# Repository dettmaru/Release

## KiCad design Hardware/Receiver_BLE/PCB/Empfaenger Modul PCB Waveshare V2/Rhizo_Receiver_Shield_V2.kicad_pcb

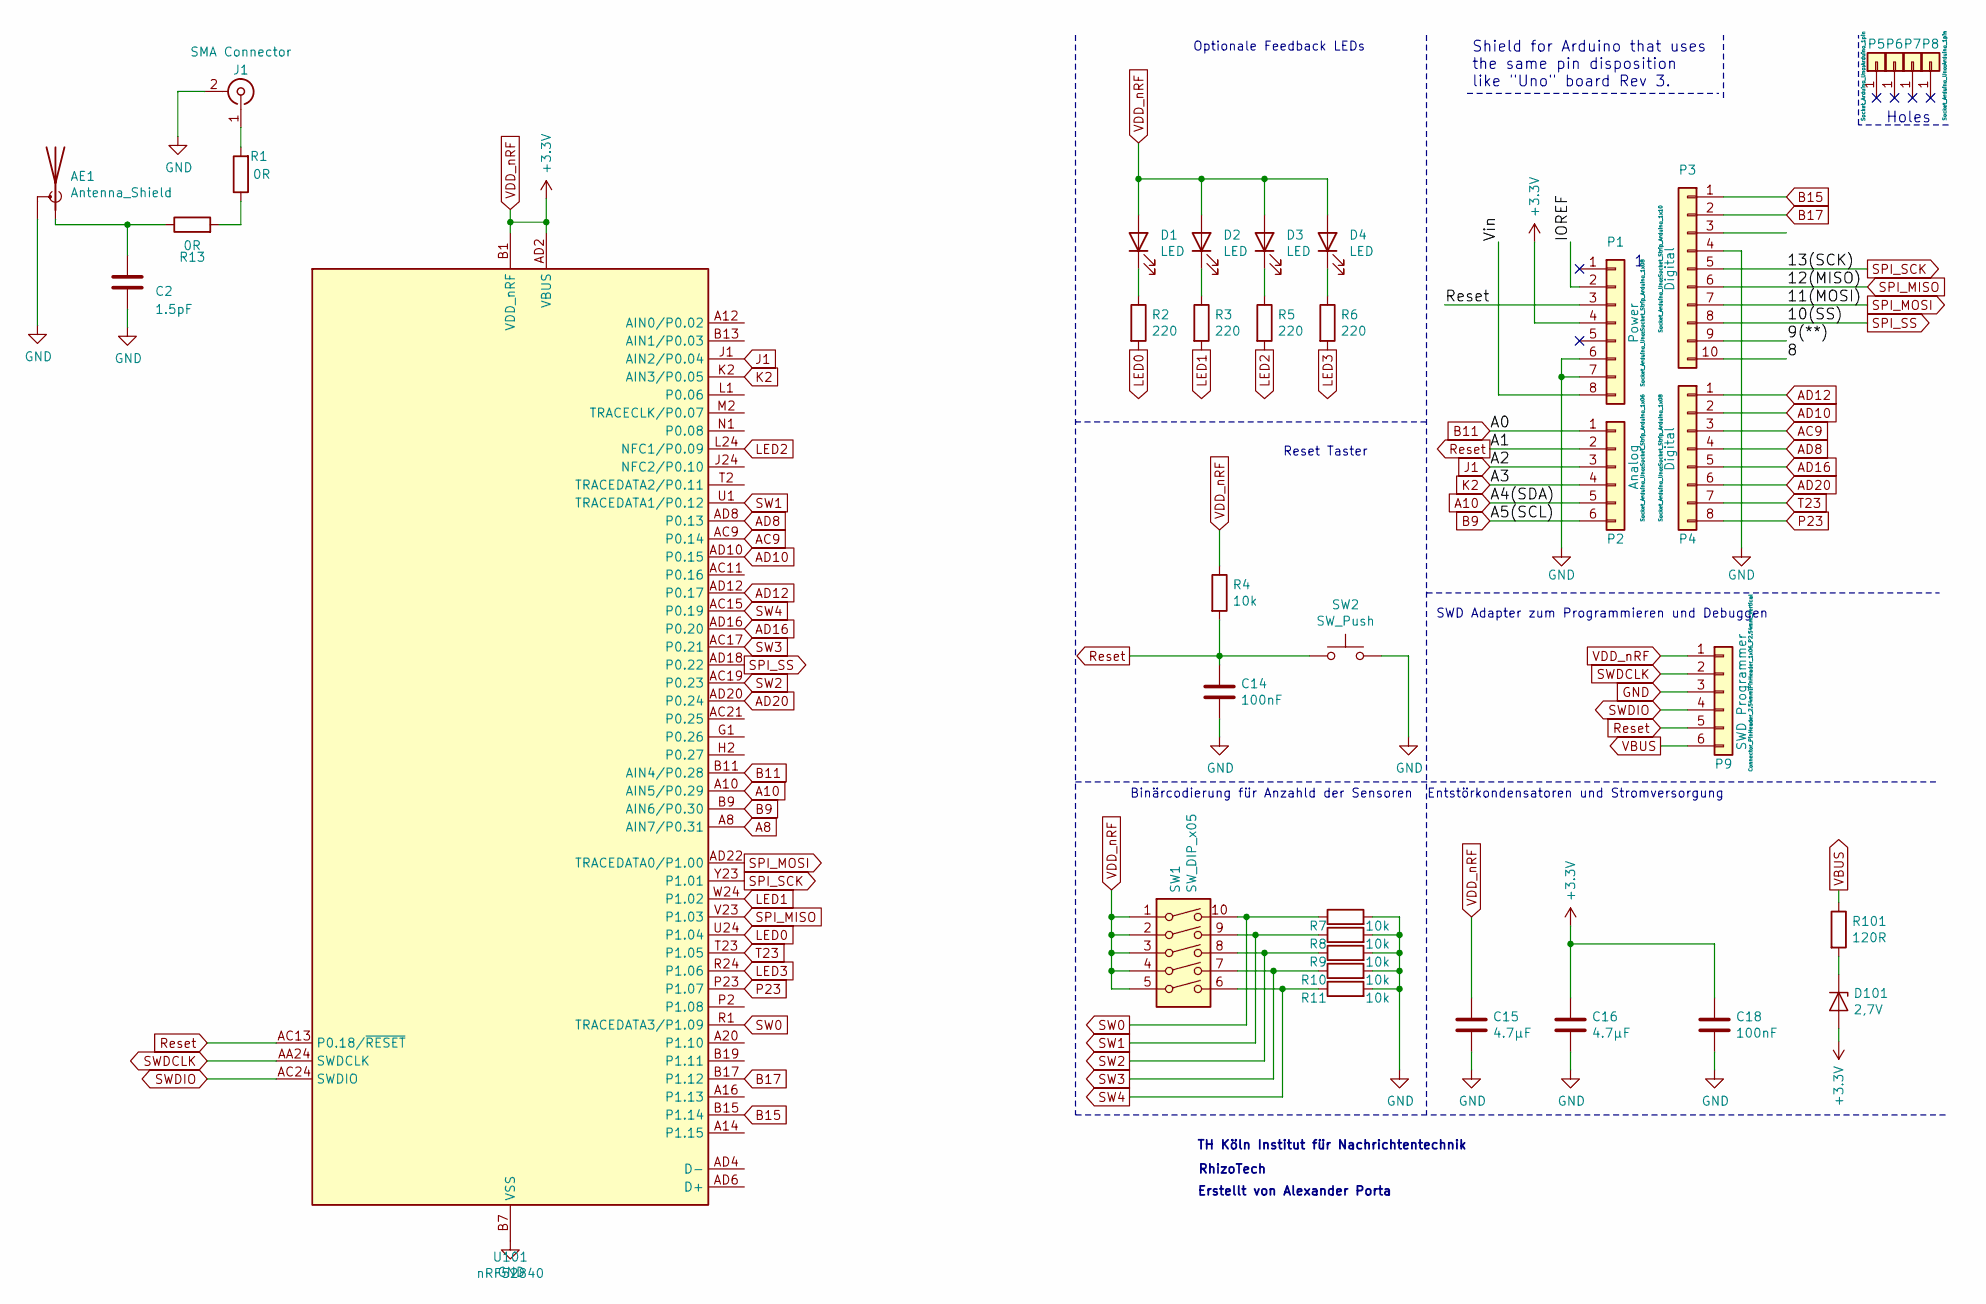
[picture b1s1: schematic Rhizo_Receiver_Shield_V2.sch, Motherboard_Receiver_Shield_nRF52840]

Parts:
AE1: Antenna_Shield; Texas_SWRA117D_2.4GHz_Left
C2: 1.5pF; C_0603_1608Metric_Pad1.08x0.95mm_HandSolder
C14, C18: 100nF; C_0603_1608Metric_Pad1.08x0.95mm_HandSolder
C15, C16: 4.7µF; C_0603_1608Metric_Pad1.08x0.95mm_HandSolder
D1, D2, D3, D4: LED; LED_0603_1608Metric
D101: 2,7V; D_0603_1608Metric
J1: SMA Connector; U.FL_Hirose_U.FL-R-SMT-1_Vertical
P1: Power; Socket_Strip_Arduino_1x08
P2: Analog; Socket_Strip_Arduino_1x06
P3: Digital; Socket_Strip_Arduino_1x10
P4: Digital; Socket_Strip_Arduino_1x08
P5, P6, P7, P8: CONN_01X01; Arduino_1pin
P9: SWD Programmer; PinHeader_1x06_P2.54mm_Vertical
R1, R13: 0R; R_0603_1608Metric
R2, R3, R5, R6: 220; R_0603_1608Metric
R4, R7, R8, R9, R10, R11: 10k; R_0603_1608Metric
R101: 120R; R_0603_1608Metric
SW1: SW_DIP_x05; SW_DIP_SPSTx05_Slide_6.7x14.26mm_W6.73mm_P2.54mm_LowProfile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
SW2: SW_Push; SW_SPST_EVQQ2
U101: nRF52840; Waveshare_nRF528840

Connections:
/8: P3.10
/9(**): P3.9
/IOREF: P1.2
/Vin: P1.8
A8: U101.A8 (AIN7/P0.31)
A10: P2.5, U101.A10 (AIN5/P0.29)
AC9: P4.3, U101.AC9 (P0.14)
AD8: P4.4, U101.AD8 (P0.13)
AD10: P4.2, U101.AD10 (P0.15)
AD12: P4.1, U101.AD12 (P0.17)
AD16: P4.5, U101.AD16 (P0.20)
AD20: P4.6, U101.AD20 (P0.24)
B9: P2.6, U101.B9 (AIN6/P0.30)
B11: P2.1, U101.B11 (AIN4/P0.28)
B15: P3.1, U101.B15 (P1.14)
B17: P3.2, U101.B17 (P1.12)
GND: AE1.2 (Shield), C2.2, C14.2, C15.2, C16.2, C18.2, J1.2 (Ext), P1.6, P1.7, P3.4, P9.3, R7.2, R8.2, R9.2, R10.2, R11.2, SW2.2, U101.B7 (VSS)
J1: P2.3, U101.J1 (AIN2/P0.04)
K2: P2.4, U101.K2 (AIN3/P0.05)
LED0: R2.2, U101.U24 (P1.04)
LED1: R3.2, U101.W24 (P1.02)
LED2: R5.2, U101.L24 (NFC1/P0.09)
LED3: R6.2, U101.R24 (P1.06)
unnamed: AE1.1 (A), C2.1, R13.1
unnamed: D1.1 (K), R2.1
unnamed: D2.1 (K), R3.1
unnamed: D3.1 (K), R5.1
unnamed: D4.1 (K), R6.1
unnamed: D101.1 (K), R101.2
unnamed: J1.1 (In), R1.2
unnamed: R1.1, R13.2
P23: P4.8, U101.P23 (P1.07)
Reset: C14.1, P1.3, P2.2, P9.5, R4.2, SW2.1, U101.AC13 (P0.18/~RESET)
SPI_MISO: P3.6, U101.V23 (P1.03)
SPI_MOSI: P3.7, U101.AD22 (TRACEDATA0/P1.00)
SPI_SCK: P3.5, U101.Y23 (P1.01)
SPI_SS: P3.8, U101.AD18 (P0.22)
SW0: R7.1, SW1.10, U101.R1 (TRACEDATA3/P1.09)
SW1: R8.1, SW1.9, U101.U1 (TRACEDATA1/P0.12)
SW2: R9.1, SW1.8, U101.AC19 (P0.23)
SW3: R10.1, SW1.7, U101.AC17 (P0.21)
SW4: R11.1, SW1.6, U101.AC15 (P0.19)
SWDCLK: P9.2, U101.AA24 (SWDCLK)
SWDIO: P9.4, U101.AC24 (SWDIO)
T23: P4.7, U101.T23 (P1.05)
VBUS: P9.6, R101.1
VDD_nRF: C15.1, C16.1, C18.1, D1.2 (A), D2.2 (A), D3.2 (A), D4.2 (A), D101.2 (A), P1.4, P9.1, R4.1, SW1.1, SW1.2, SW1.3, SW1.4, SW1.5, U101.AD2 (VBUS), U101.B1 (VDD_nRF)

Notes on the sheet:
Binärcodierung für Anzahld der Sensoren
Optionale Feedback LEDs
TH Köln Institut für Nachrichtentechnik
Erstellt von Alexander Porta
RhizoTech
Reset Taster
Entstörkondensatoren und Stromversorgung
SWD Adapter zum Programmieren und Debuggen
Shield for Arduino that uses the same pin disposition like "Uno" board Rev 3.
Holes

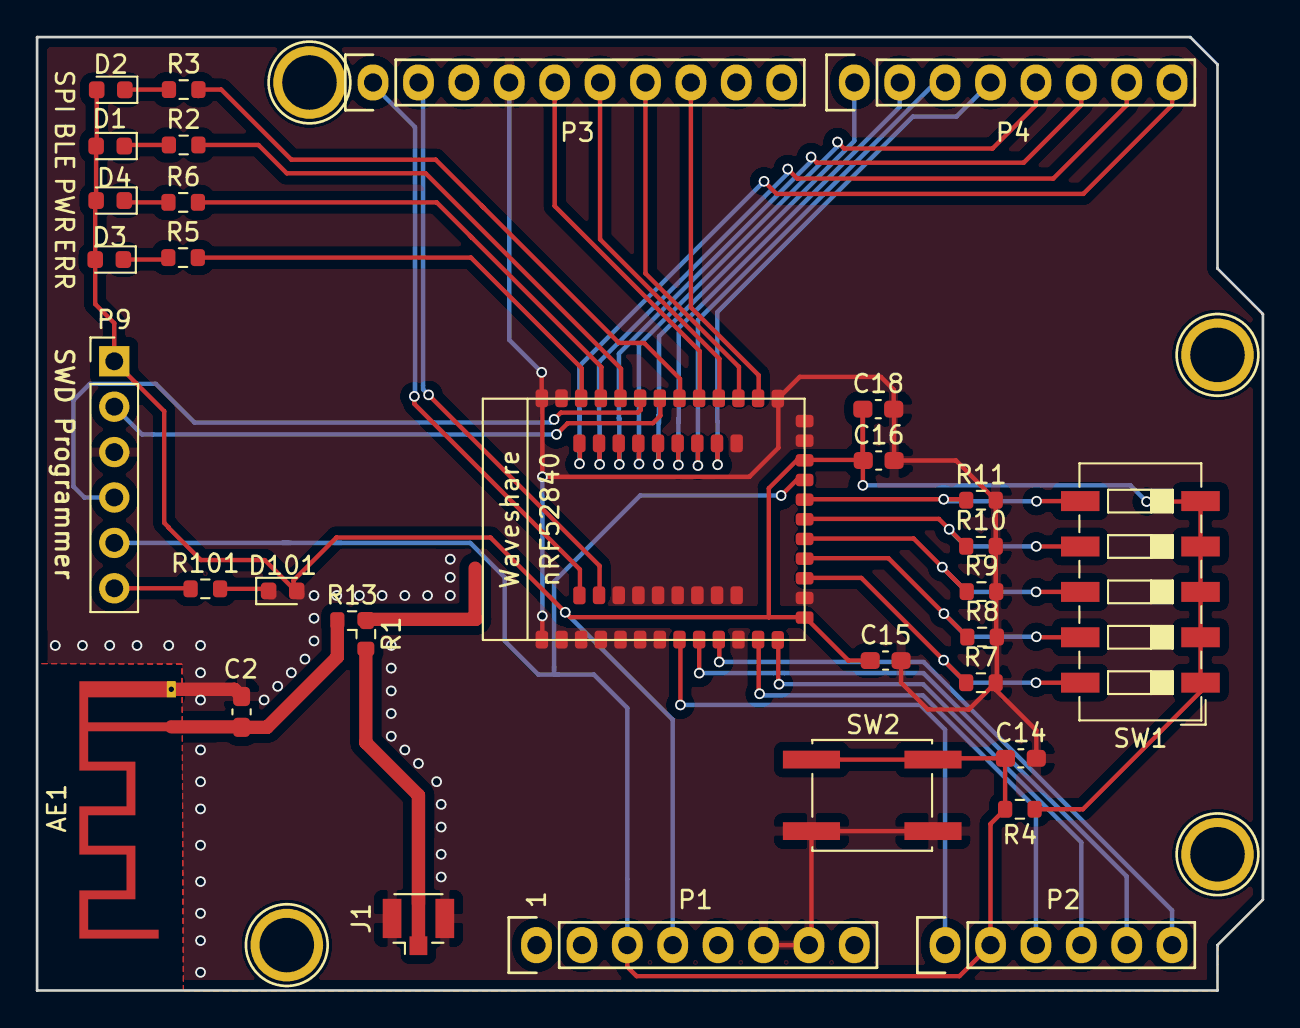
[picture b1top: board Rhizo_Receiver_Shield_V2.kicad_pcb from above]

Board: 2 copper layers, 68.6 x 53.3 mm, 37 parts (0 on the bottom side), 42 nets.

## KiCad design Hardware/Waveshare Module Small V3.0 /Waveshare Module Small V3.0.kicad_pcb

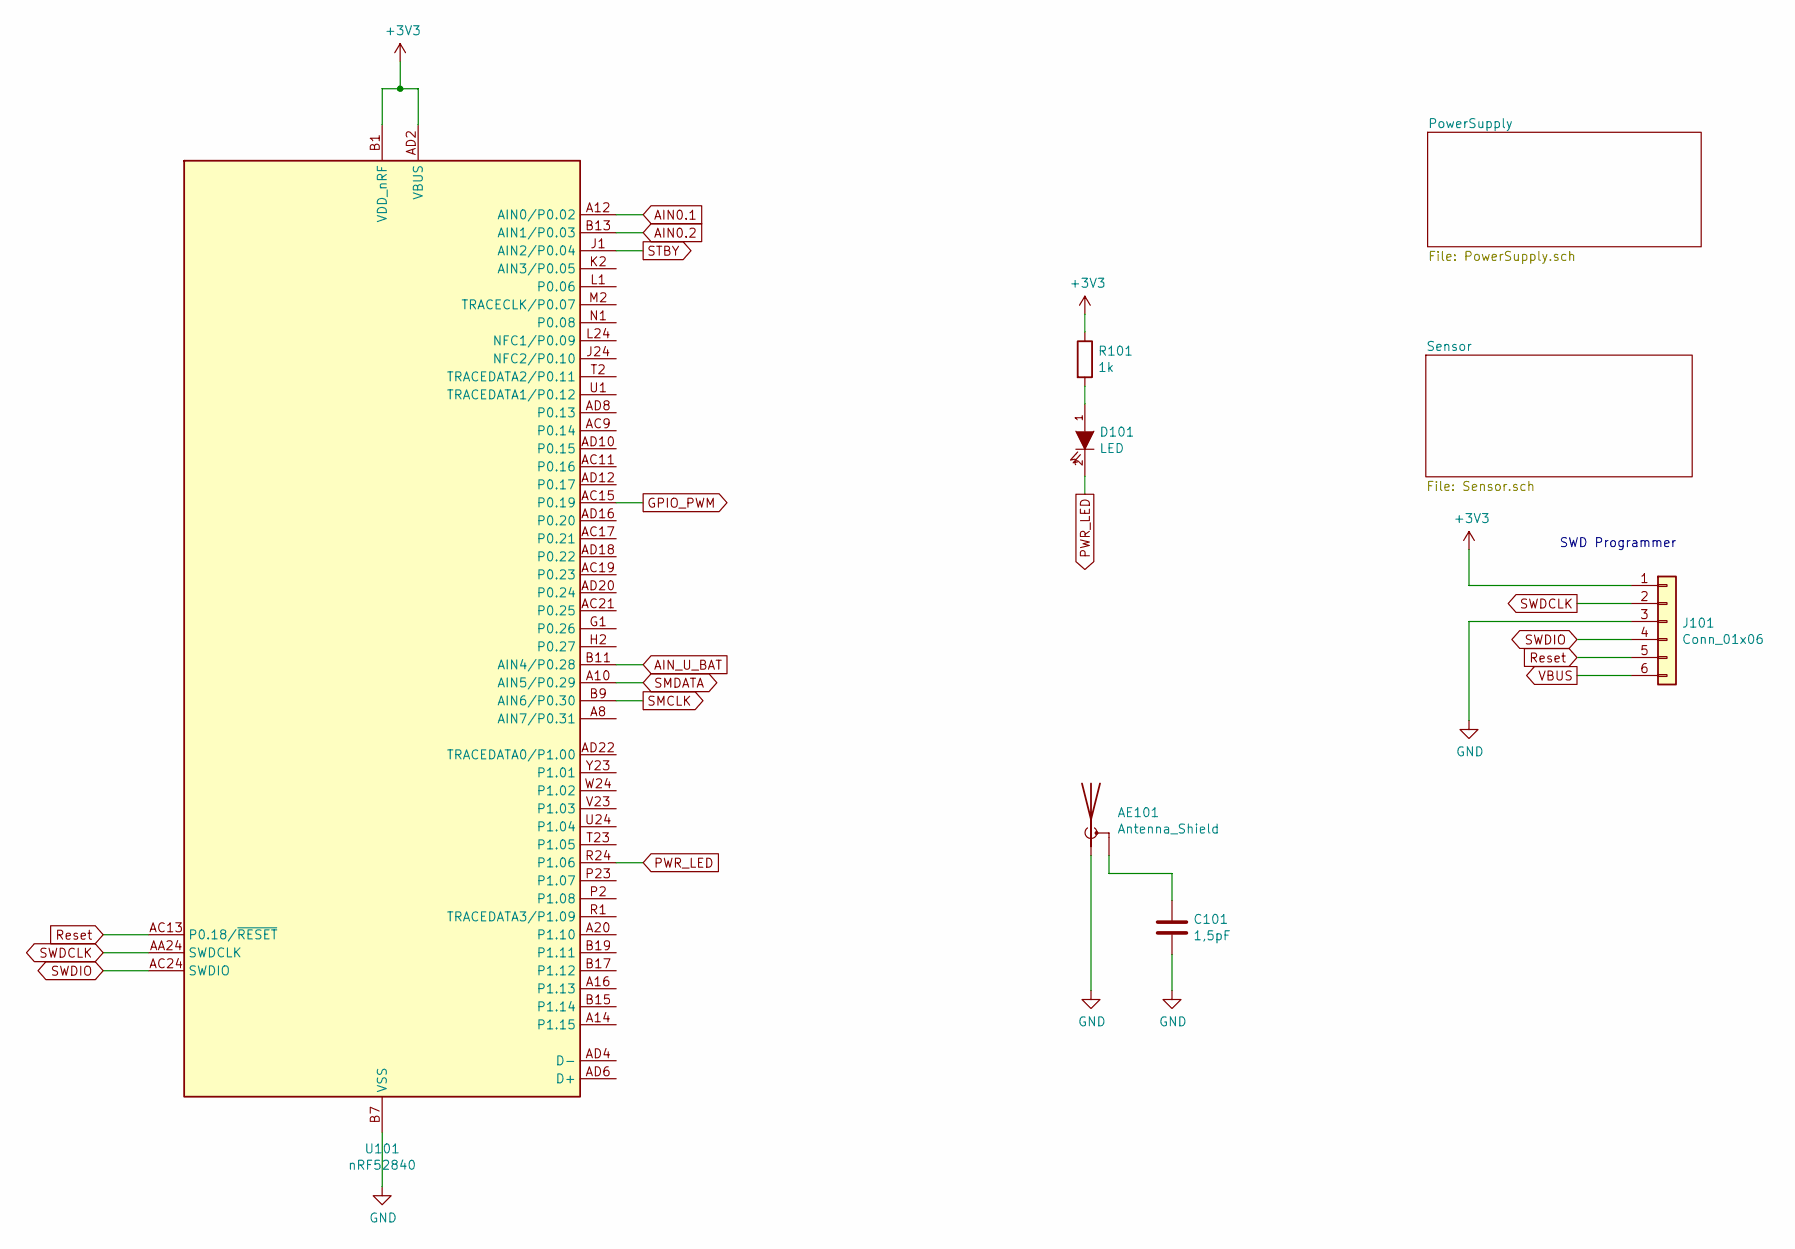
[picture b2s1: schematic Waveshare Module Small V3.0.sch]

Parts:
AE101: Antenna_Shield; Texas_SWRA117D_2.4GHz_Right
C101: 1,5pF; C_0603_1608Metric_Pad1.08x0.95mm_HandSolder
D101: LED; LED_0603_1608Metric_Pad1.05x0.95mm_HandSolder
J101: Conn_01x06; PinHeader_1x06_P2.54mm_Vertical
R101: 1k; R_0603_1608Metric_Pad0.98x0.95mm_HandSolder
U101: nRF52840; Waveshare_nRF528840

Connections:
+3V3: J101.1, R101.1, U101.AD2 (VBUS), U101.B1 (VDD_nRF); also elsewhere on the board
AIN0.1: U101.A12 (AIN0/P0.02); also elsewhere on the board
AIN0.2: U101.B13 (AIN1/P0.03); also elsewhere on the board
AIN_U_BAT: U101.B11 (AIN4/P0.28); also elsewhere on the board
GND: AE101.1 (A), C101.2, J101.3, U101.B7 (VSS); also elsewhere on the board
GPIO_PWM: U101.AC15 (P0.19); also elsewhere on the board
unnamed: AE101.2 (Shield), C101.1
unnamed: D101.1 (A), R101.2
PWR_LED: D101.2 (K), U101.R24 (P1.06)
Reset: J101.5, U101.AC13 (P0.18/~RESET)
SMCLK: U101.B9 (AIN6/P0.30); also elsewhere on the board
SMDATA: U101.A10 (AIN5/P0.29); also elsewhere on the board
STBY: U101.J1 (AIN2/P0.04); also elsewhere on the board
SWDCLK: J101.2, U101.AA24 (SWDCLK)
SWDIO: J101.4, U101.AC24 (SWDIO)
VBUS: J101.6

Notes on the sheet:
SWD Programmer

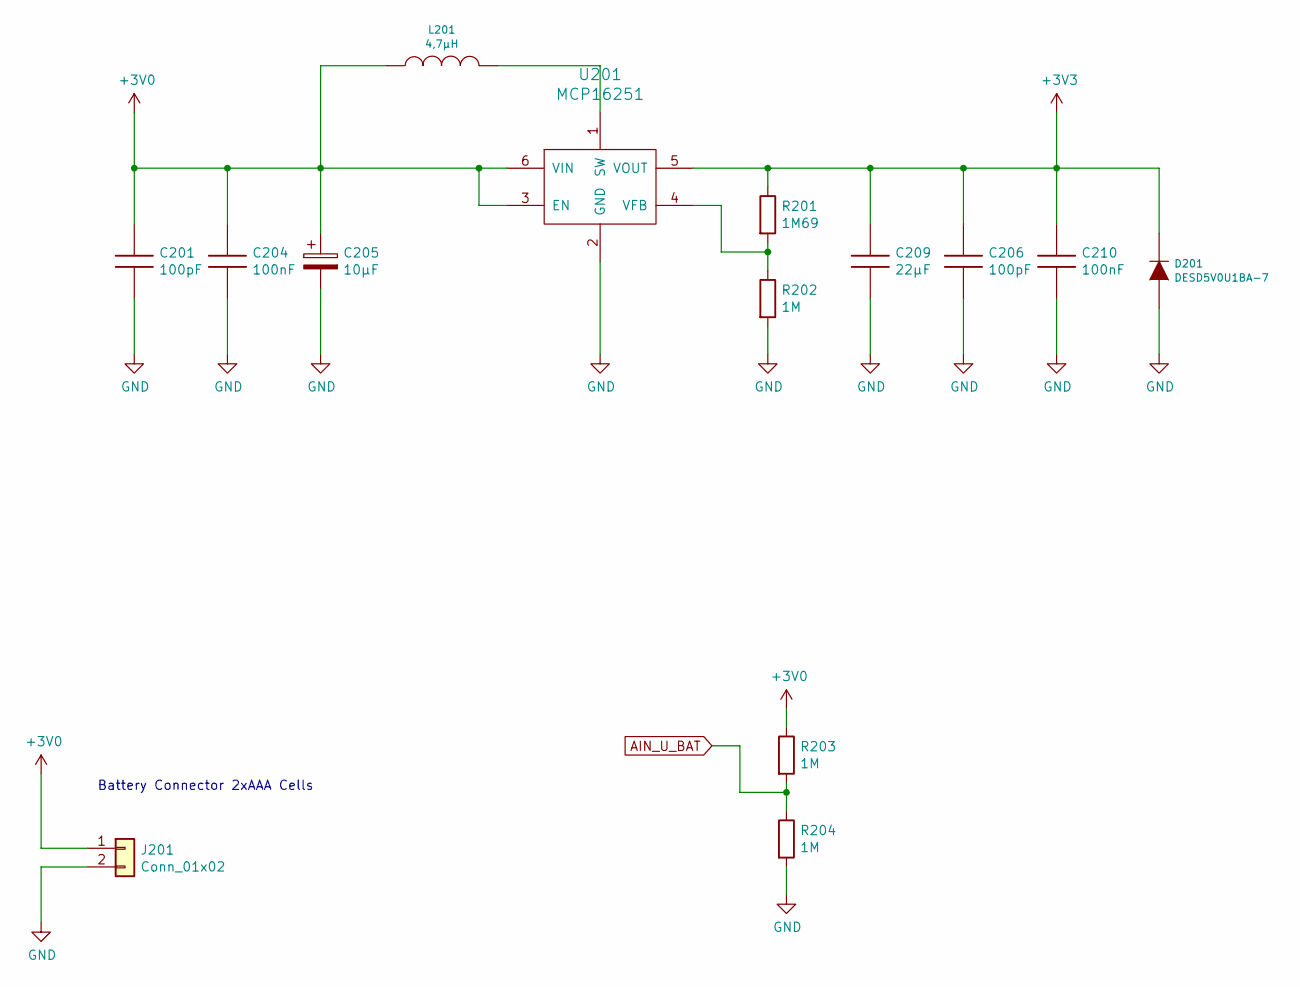
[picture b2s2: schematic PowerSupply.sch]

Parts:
C201, C206: 100pF; C_0603_1608Metric_Pad1.08x0.95mm_HandSolder
C204, C210: 100nF; C_0603_1608Metric_Pad1.08x0.95mm_HandSolder
C205: 10µF; R_0603_1608Metric_Pad0.98x0.95mm_HandSolder
C209: 22µF; CP_Elec_4x5.4
D201: DESD5V0U1BA-7; D_0603_1608Metric_Pad1.05x0.95mm_HandSolder
J201: Conn_01x02; PinHeader_1x02_P2.54mm_Vertical
L201: 4,7µH; L_Bourns-SRN4018
R201: 1M69; R_0603_1608Metric_Pad0.98x0.95mm_HandSolder
R202, R203, R204: 1M; R_0603_1608Metric_Pad0.98x0.95mm_HandSolder
U201: MCP16251; SOT-23-6_Handsoldering

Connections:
+3V0: C201.1, C204.1, C205.1, J201.1, L201.1, R203.1, U201.3 (EN), U201.6 (VIN)
+3V3: C206.1, C209.1, C210.1, D201.2 (K), R201.1, U201.5 (VOUT); also elsewhere on the board
AIN_U_BAT: R203.2, R204.1; also elsewhere on the board
GND: C201.2, C204.2, C205.2, C206.2, C209.2, C210.2, D201.1 (A), J201.2, R202.2, R204.2, U201.2 (GND); also elsewhere on the board
unnamed: L201.2, U201.1 (SW)
unnamed: R201.2, R202.1, U201.4 (VFB)

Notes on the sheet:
Battery Connector 2xAAA Cells

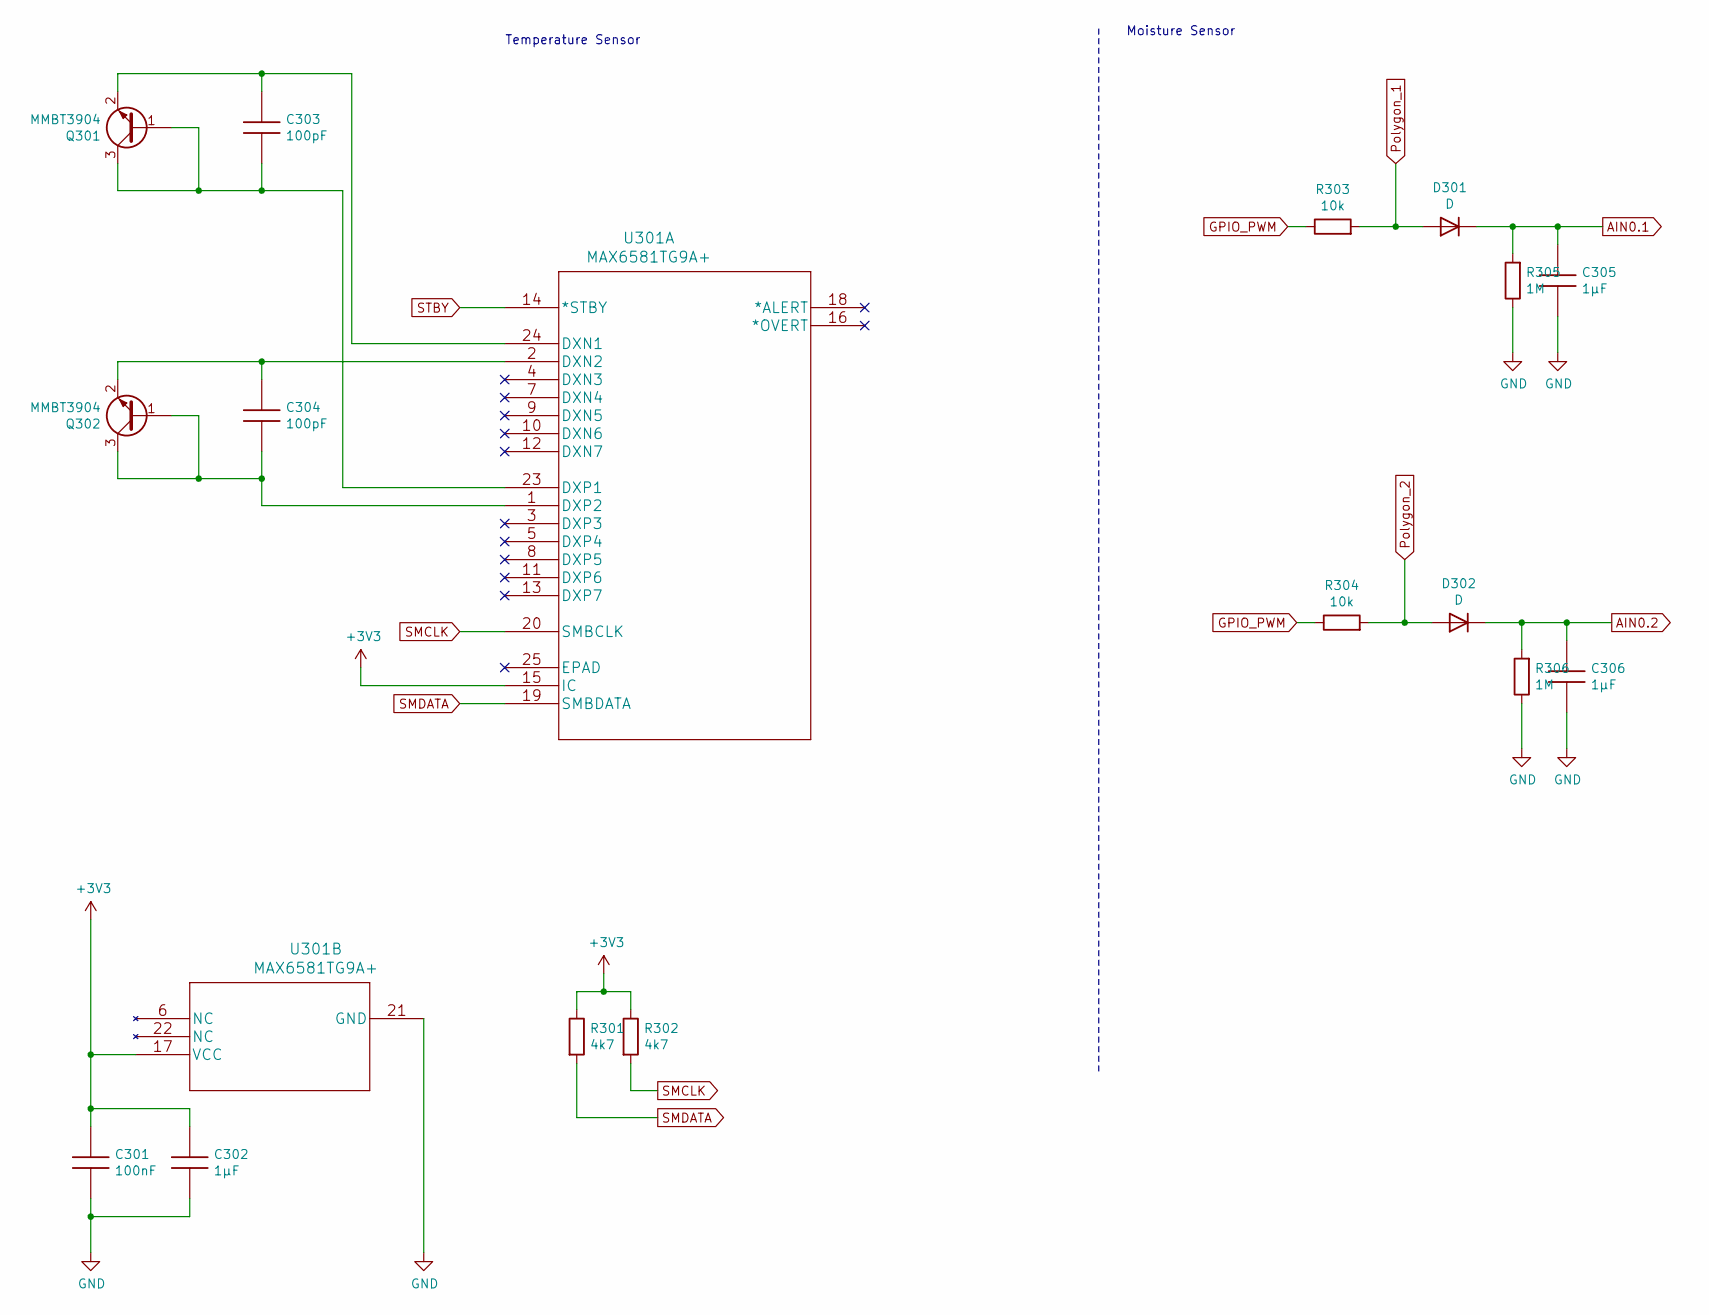
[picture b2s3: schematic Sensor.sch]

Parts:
C301: 100nF; C_0603_1608Metric_Pad1.08x0.95mm_HandSolder
C302, C305, C306: 1µF; C_0603_1608Metric_Pad1.08x0.95mm_HandSolder
C303, C304: 100pF; C_0603_1608Metric_Pad1.08x0.95mm_HandSolder
D301, D302: D; D_0603_1608Metric_Pad1.05x0.95mm_HandSolder
Q301, Q302: MMBT3904; SOT-23
R301, R302: 4k7; R_0603_1608Metric_Pad0.98x0.95mm_HandSolder
R303, R304: 10k; R_0603_1608Metric_Pad0.98x0.95mm_HandSolder
R305, R306: 1M; R_0603_1608Metric_Pad0.98x0.95mm_HandSolder
U301: MAX6581TG9A+; HVQFN-24-1EP_4x4mm_P0.5mm_EP2.5x2.5mm

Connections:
+3V3: C301.1, C302.1, R301.1, R302.1, U301.15 (IC), U301.17 (VCC); also elsewhere on the board
AIN0.1: C305.1, D301.1 (K), R305.2; also elsewhere on the board
AIN0.2: C306.1, D302.1 (K), R306.2; also elsewhere on the board
GND: C301.2, C302.2, C305.2, C306.2, R305.1, R306.1, U301.21 (GND); also elsewhere on the board
GPIO_PWM: R303.1, R304.1; also elsewhere on the board
unnamed: C303.1, Q301.2 (E), U301.24 (DXN1)
unnamed: C303.2, Q301.1 (B), Q301.3 (C), U301.23 (DXP1)
unnamed: C304.1, Q302.2 (E), U301.2 (DXN2)
unnamed: C304.2, Q302.1 (B), Q302.3 (C), U301.1 (DXP2)
Polygon_1: D301.2 (A), R303.2
Polygon_2: D302.2 (A), R304.2
SMCLK: R302.2, U301.20 (SMBCLK); also elsewhere on the board
SMDATA: R301.2, U301.19 (SMBDATA); also elsewhere on the board
STBY: U301.14 (*STBY); also elsewhere on the board

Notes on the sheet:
Moisture Sensor
Temperature Sensor

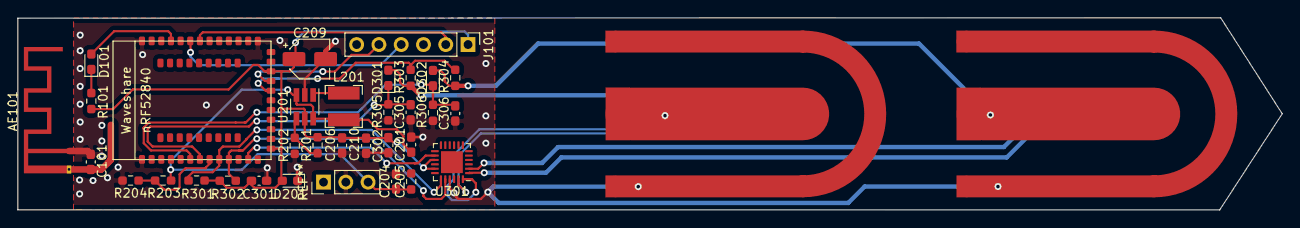
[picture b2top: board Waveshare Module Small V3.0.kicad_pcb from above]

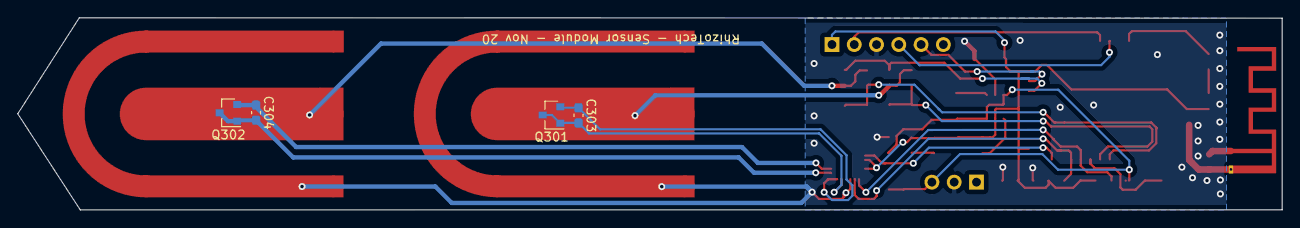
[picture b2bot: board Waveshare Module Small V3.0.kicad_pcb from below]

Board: 2 copper layers, 144.1 x 21.9 mm, 36 parts (4 on the bottom side), 24 nets.

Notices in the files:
Software/Motherboard_BLE_2s/Src/gpio.c:
© Copyright (c) 2020 STMicroelectronics.
All rights reserved.
This software component is licensed by ST under Ultimate Liberty license
(C) COPYRIGHT STMicroelectronics *****END OF FILE
